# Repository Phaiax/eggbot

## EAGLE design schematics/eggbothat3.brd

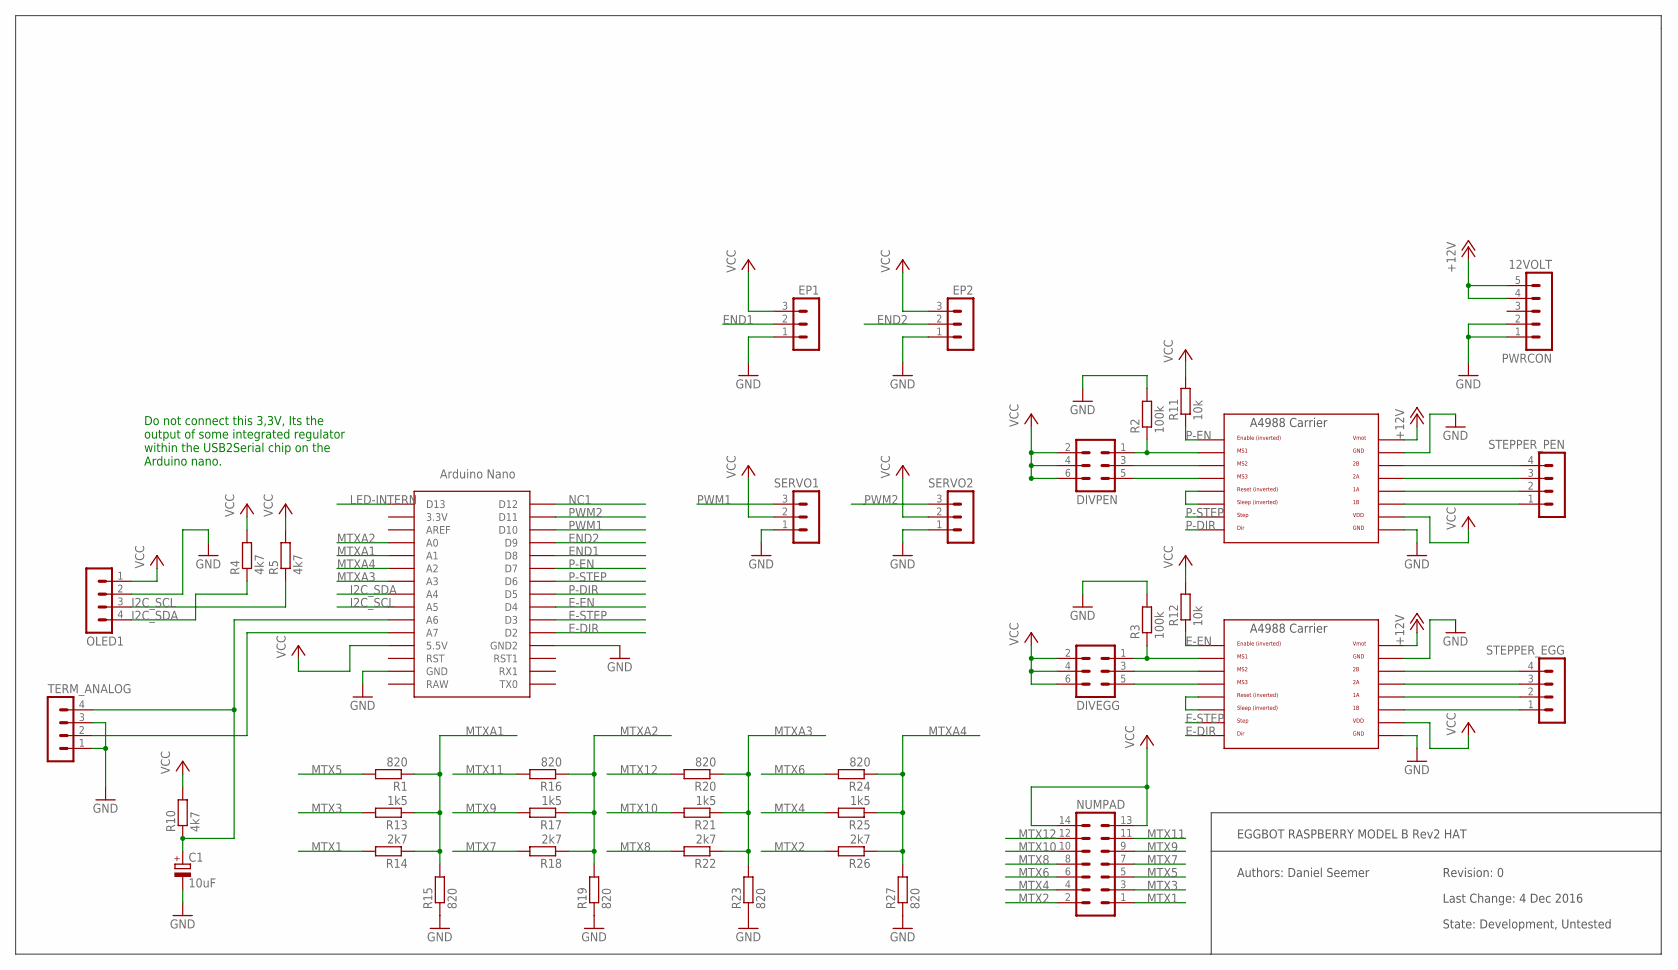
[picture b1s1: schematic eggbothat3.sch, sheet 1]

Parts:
12VOLT: PWRCON; MA05-1
C1: 10uF; E2,5-5
DIVEGG: MA03-2
DIVPEN: MA03-2
EP1, EP2: MA03-1
NUMPAD: MA07-2
OLED1: MA04-1
R1, R15, R16, R19, R20, R23, R24, R27: 820; R1206
R2, R3: 100k; R1206
R4, R5, R10: 4k7; R1206
R11, R12: 10k; R1206
R13, R17, R21, R25: 1k5; R1206
R14, R18, R22, R26: 2k7; R1206
SERVO1, SERVO2: MA03-1
STEPPER_EGG: MA04-1
STEPPER_PEN: MA04-1
TERM_ANALOG: MA04-1
U$1, U$2: A4988BREAKOUT
U$4: NANO

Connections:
+12V: 12VOLT.4, 12VOLT.5, U$1.VMOT, U$2.VMOT
E-DIR: U$2.DIR, U$4.D2
E-EN: R12.1, U$2.EN, U$4.D4
E-STEP: U$2.STEP, U$4.D3
END1: EP1.2, U$4.D8
END2: EP2.2, U$4.D9
GND: 12VOLT.1, 12VOLT.2, C1.-, EP1.1, EP2.1, OLED1.2, R2.2, R3.2, R15.1, R19.1, R23.1, R27.1, SERVO1.1, SERVO2.1, TERM_ANALOG.1, TERM_ANALOG.3, U$1.GND, U$1.GND@0 (GND), U$2.GND, U$2.GND@0 (GND), U$4.GND, U$4.GND1 (GND2)
I2C_SCL: OLED1.3, R5.1, U$4.A5
I2C_SDA: OLED1.4, R4.1, U$4.A4
LED-INTERN: U$4.D13
MTX1: NUMPAD.1, R14.2
MTX2: NUMPAD.2, R26.2
MTX3: NUMPAD.3, R13.2
MTX4: NUMPAD.4, R25.2
MTX5: NUMPAD.5, R1.2
MTX6: NUMPAD.6, R24.2
MTX7: NUMPAD.7, R18.2
MTX8: NUMPAD.8, R22.2
MTX9: NUMPAD.9, R17.2
MTX10: NUMPAD.10, R21.2
MTX11: NUMPAD.11, R16.2
MTX12: NUMPAD.12, R20.2
MTXA1: R1.1, R13.1, R14.1, R15.2, U$4.A1
MTXA2: R16.1, R17.1, R18.1, R19.2, U$4.A0
MTXA3: R20.1, R21.1, R22.1, R23.2, U$4.A3
MTXA4: R24.1, R25.1, R26.1, R27.2, U$4.A2
unnamed: STEPPER_PEN.4, U$1.2B
unnamed: STEPPER_PEN.3, U$1.2A
unnamed: STEPPER_PEN.2, U$1.1A
unnamed: STEPPER_PEN.1, U$1.1B
unnamed: STEPPER_EGG.4, U$2.2B
unnamed: STEPPER_EGG.3, U$2.2A
unnamed: STEPPER_EGG.2, U$2.1A
unnamed: STEPPER_EGG.1, U$2.1B
unnamed: DIVPEN.3, U$1.MS2
unnamed: DIVPEN.1, R2.1, U$1.MS1
unnamed: DIVPEN.5, U$1.MS3
unnamed: DIVEGG.3, U$2.MS2
unnamed: DIVEGG.1, R3.1, U$2.MS1
unnamed: DIVEGG.5, U$2.MS3
unnamed: U$1.RST, U$1.SLP (SLEEP)
unnamed: U$2.RST, U$2.SLP (SLEEP)
unnamed: C1.+, R10.1, TERM_ANALOG.4, U$4.A6
unnamed: TERM_ANALOG.2, U$4.A7
NC1: U$4.D12
P-DIR: U$1.DIR, U$4.D5
P-EN: R11.1, U$1.EN, U$4.D7
P-STEP: U$1.STEP, U$4.D6
PWM1: SERVO1.3, U$4.D10
PWM2: SERVO2.3, U$4.D11
VCC: DIVEGG.2, DIVEGG.4, DIVEGG.6, DIVPEN.2, DIVPEN.4, DIVPEN.6, EP1.3, EP2.3, NUMPAD.13, NUMPAD.14, OLED1.1, R4.2, R5.2, R10.2, R11.2, R12.2, SERVO1.2, SERVO2.2, U$1.VDD, U$2.VDD, U$4.5V (5.5V)

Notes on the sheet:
Do not connect this 3,3V, Its the output of some integrated regulator within the USB2Serial chip on the Arduino nano.
EGGBOT RASPBERRY MODEL B Rev2 HAT
Authors: Daniel Seemer
Last Change: 4 Dec 2016
State: Development, Untested
Revision: 0

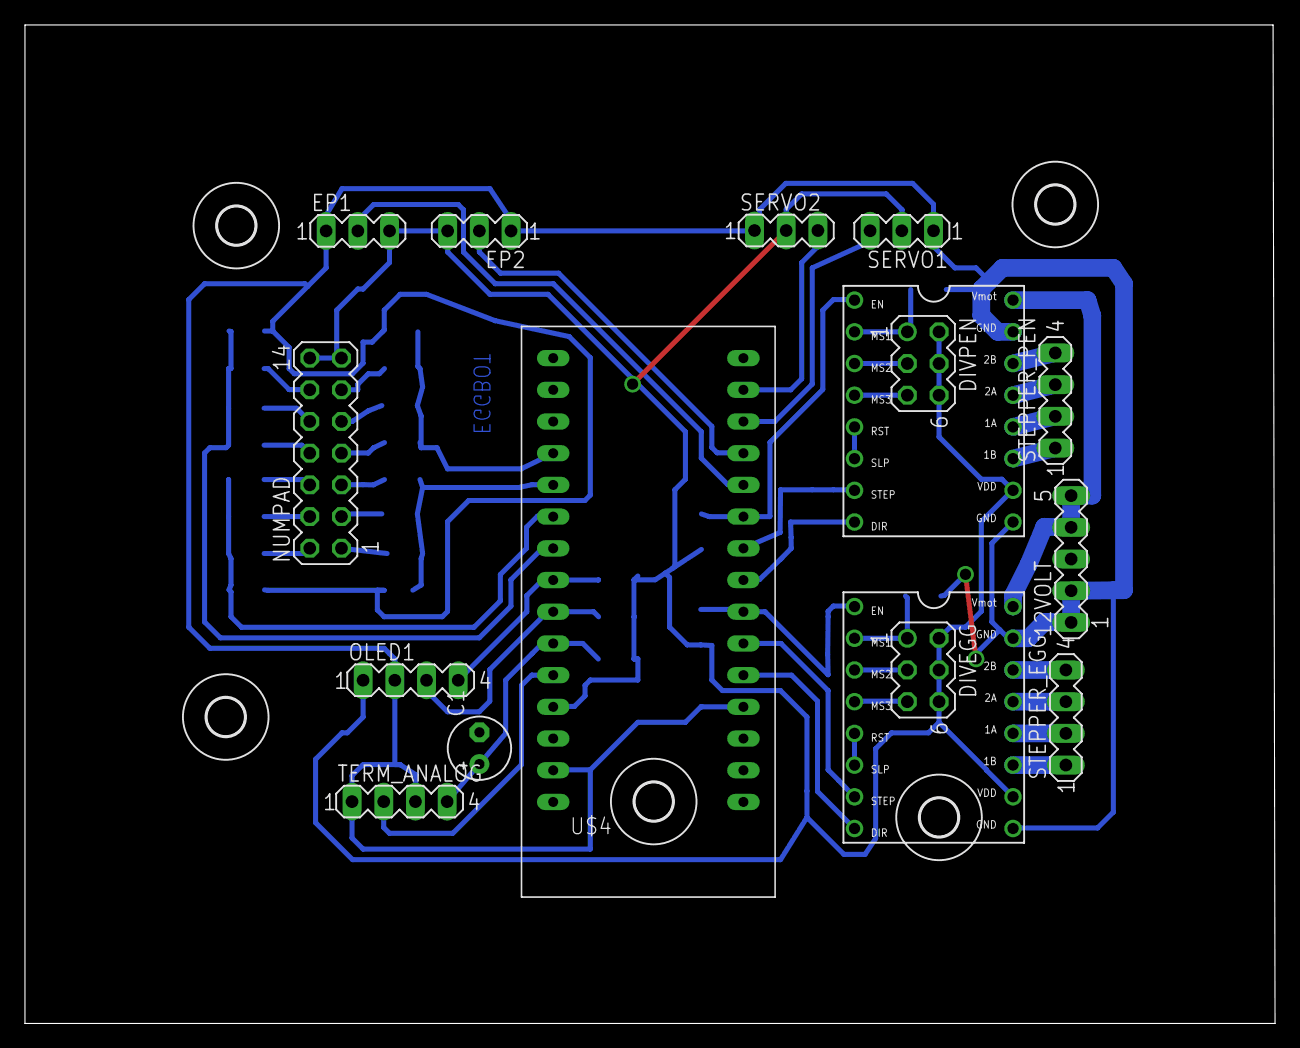
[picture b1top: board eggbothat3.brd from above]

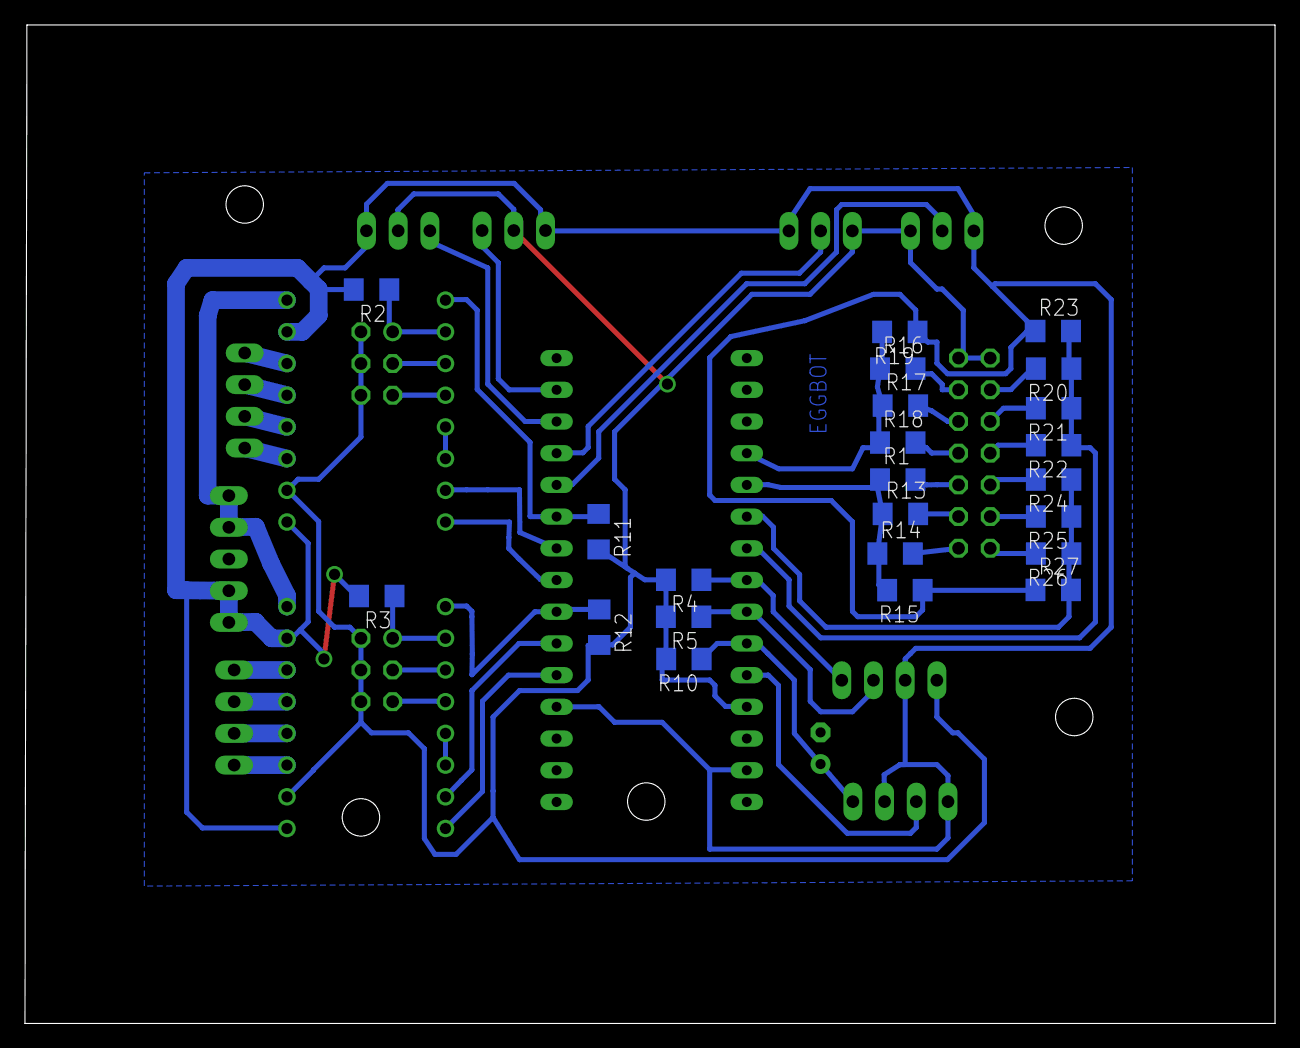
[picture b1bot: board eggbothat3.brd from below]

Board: 2 copper layers, 100.2 x 80.0 mm, 44 parts (23 on the bottom side), 49 nets.

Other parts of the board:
U$3, U$5, U$6, U$7, U$8: 3,0

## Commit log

2016-12-03 Eggbot openscad sketch
2016-12-04 schematics and board
2016-12-04 Oled Datasheets
2016-12-04 PI stl
2016-12-04 BOM backup
2016-12-04 continue scratching: PI
2016-12-04 schematic fixes
2016-12-04 try pen motor elevator
2016-12-08 Add ring holders, refactor
2016-12-09 Second version of schematics
2016-12-11 versions 2,3 of electronics
2016-12-13 Board update (don't know exactly what)
2016-12-13 3D model update
2016-12-13 Arduino and host test code
2016-12-13 Sublime project file
2016-12-17 Communication between Arduino and host
2016-12-21 gears and eggbot stls from thingiverse as comparision
2016-12-21 model update
2016-12-21 communication and servo tests
2016-12-21 schematic change?
2016-12-21 ready for printing
2016-12-21 Nema screws
2016-12-21 switch to lm10uu, export as stl
